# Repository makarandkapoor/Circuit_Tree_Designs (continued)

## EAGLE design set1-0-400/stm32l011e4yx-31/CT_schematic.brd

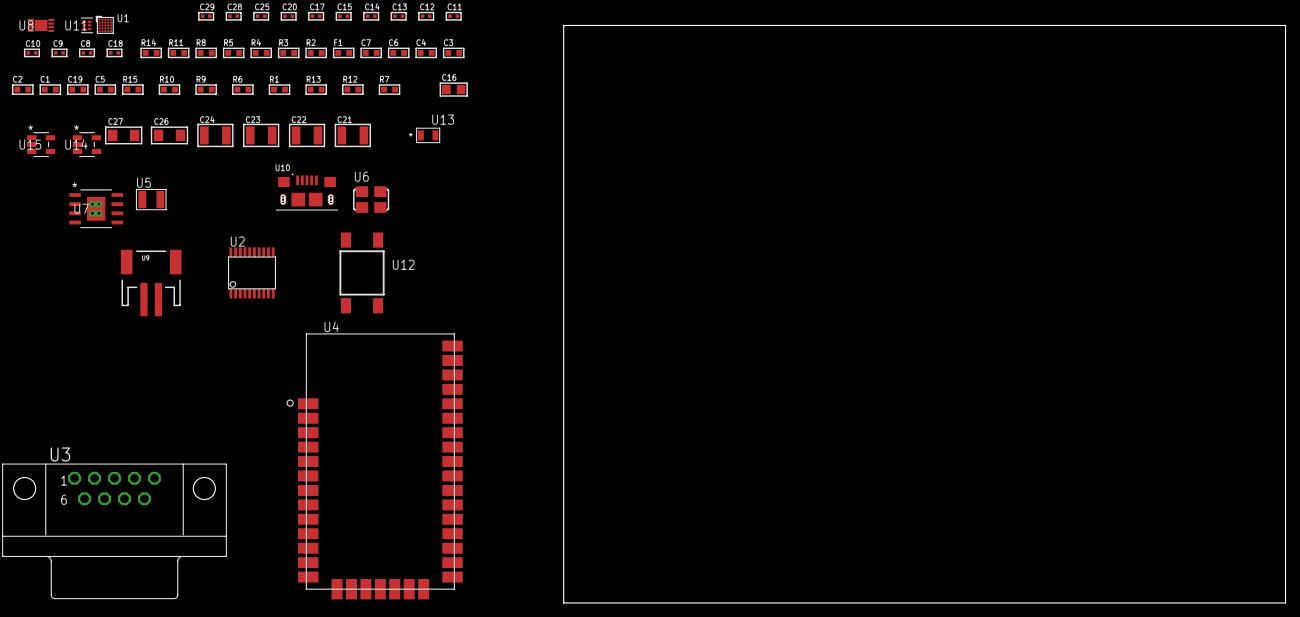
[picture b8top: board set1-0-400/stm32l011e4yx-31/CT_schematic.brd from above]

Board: 2 copper layers, 60 parts (0 on the bottom side), 37 nets, no tracks yet.

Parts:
C1, C2, C3, C4: 1e-07; C0603
C5: 4.7e-06; C0603
C6: 1e-08; C0603
C7: 1e-06; C0603
C8, C9: 1e-11; C0402
C10, C11, C12, C13, C14, C15, C17, C25: 1e-07; C0402
C16: 1e-05; C0805
C18: 4.7e-11; C0402
C19: 8.2e-12; C0603
C20, C28, C29: 1e-08; C0402
C21, C22, C23, C24: 1e-05; C1210
C26, C27: 1e-05; C1206
F1: 240.0; L0603
R1, R6, R9, R10, R15: 10000.0; R0603
R2: 1000.0; R0603
R3: 1600.5; R0603
R4, R5: 4700.0; R0603
R7: 4031.5447154472; R0603
R8: 2200.0; R0603
R11: 9100.0; R0603
R12: 680000.0; R0603
R13: 120000.0; R0603
R14: 2000.0; R0603
U1: STM32L011E4Y6; WLCSP25
U2: SP3203ECY-L/TR; TSSOP20-I
U3: 182-009-113R531; 182-009-MALE
U4: XB24CZ7UIS-004
U5: ABS07-32.768KHZ-7-T
U6: ASFL1-12MHZ-NCS; ASFL1
U7: MIC5234YME; SOIC-8_EP
U8: MCP73831T-2ACI/MC; DFN8_2X3MC
U9: S2B-PH-SM4-TB(LF)(SN); JST-2-SMD
U10: 10118193-0001LF; FCI_10118193-0001LF
U11: TPS3895ADRYR; SON-6
U12: 4-1437565-2; SW_4-1437565-2
U13: Q65110A2395; LGM67K-G1J2-24-Z
U14, U15: nc7sz125m5x; NC7SZ125M5X

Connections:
CLK_CRYSTAL_U1_B5: C8.1, U1.B5, U5.1
CLK_CRYSTAL_U1_C5: C9.1, U1.C5, U5.2
GND: C1.2, C2.2, C3.2, C4.2, C5.2, C6.2, C7.2, C8.2, C9.2, C10.2, C11.2, C14.2, C15.2, C16.2, C17.2, C18.2, C19.2, C20.2, C21.2, C22.2, C23.2, C24.2, C25.2, C26.2, C27.2, C28.2, C29.2, R2.2, R6.2, R8.2, R11.2, R13.2, R14.2, U1.E1, U2.18, U3.5, U4.1, U4.11, U4.13, U4.22, U4.35, U6.2, U7.7, U7.EPAD, U8.6, U8.9, U9.2, U10.5, U10.6, U10.7, U10.8, U10.9, U11.2, U13.C, U14.1, U14.3, U15.1, U15.3
INPUT_USBPOWER_5V: C26.1, R15.2, U8.1, U8.2, U10.1
NET_U1_A5: R6.1, U1.A5
NET_U1_C4: C6.1, C7.1, F1.1, U1.C4
NET_U1_D5: R5.1, U1.D5, U15.4
NET_U1_E4: R3.1, U1.E4, U13.A
NET_U1_E5: R1.1, U1.E5, U6.3, U12.3, U12.4
NET_U2_1: C12.1, U2.1
NET_U2_2: C14.1, U2.2
NET_U2_3: C12.2, U2.3
NET_U2_4: C13.1, U2.4
NET_U2_5: C13.2, U2.5
NET_U2_6: C15.1, U2.6
NET_U3_2: U2.14, U3.2
NET_U3_3: U2.17, U3.3
NET_U3_7: U2.13, U3.7
NET_U3_8: U2.16, U3.8
NET_U4_6: R4.1, U4.6, U14.4
NET_U7_4: R7.2, R8.1, U7.4
NET_U8_5: R15.1, U8.5
NET_U8_8: R14.1, U8.8
NET_U11_1: R10.1, R11.1, U11.1
NET_U11_3: R12.2, R13.1, U11.3
NET_U11_4: R9.1, U11.4, U14.2, U15.2
NET_U12_1: R2.1, U12.1, U12.2
PROC_LPUART1_CTS: U1.E3, U2.8
PROC_LPUART1_RTS: U1.D2, U2.10
PROC_LPUART1_RX: U1.A1, U2.11
PROC_LPUART1_TX: U1.A2, U2.7
PROC_SPI1_MISO: U1.E2, U4.17
PROC_SPI1_MOSI: U1.C3, U4.16
PROC_SPI1_NSS: U1.B3, U4.15
PROC_SPI1_SCK: U1.B2, U4.14
VCC_S1_3V7: C21.1, C22.1, C27.1, U7.5, U7.8, U8.3, U8.4, U9.1
VCC_TIER1_3V3: C1.1, C2.1, C3.1, C4.1, C5.1, C10.1, C11.1, C16.1, C17.1, C18.1, C19.1, C20.1, C23.1, C24.1, C25.1, C28.1, C29.1, F1.2, R1.2, R3.2, R4.2, R5.2, R7.1, R9.2, R10.2, R12.1, U1.D1, U2.12, U2.19, U4.2, U4.27, U6.4, U7.1, U11.6, U14.5, U15.5
